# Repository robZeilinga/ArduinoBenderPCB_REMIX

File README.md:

# ArduinoBenderPCB_REMIX
Remix of PCB for Arduino controlled Wire Bender - Eagle Files

# NB NB : The PDF diagram is Mirrored! If you want to use this to make the PCB using Toner Transfer, You will need to mirror the PDF before Printing. 

A friend of mine wanted to build the AWESOME arduino controlled Wire Bender project by **How To Mechatronics**

project URL : https://howtomechatronics.com/projects/arduino-3d-wire-bending-machine/

But the provided PCB is Dual-sided. 

the PCB here is a Single Sided Version with thick tracks to help with Toner Transfer etc.

Please Note that Pin Assigments are changed if you use this PCB you will have to modify the code provided by the original project.

**Notable Changes :**

1. 7805 regulator has been removed as the Arduino NANO can regulate 12V with the built in regulator.
1. spare Digital pins D8 -- D12 have pads for optional pull up Resistors.
1. All Analogue Pins are broken out.
1. Stepper Driver Resolution is set via solder jumpers on the Copper side of the board.

if you use this PCB, please note the following changes need to be made in the Definition part of the Arduino Code.

ORIGINAL CODE 
-----------------
    // Define the stepper motors and the pins the will use
    AccelStepper feederStepper(1, 5, 6); // (Type:driver, STEP, DIR)
    AccelStepper zAxisStepper(1, 7, 8);
    AccelStepper benderStepper(1, 9, 10);

CHANGE TO
---------

    // Define the stepper motors and the pins the will use
    AccelStepper feederStepper(1, 6, 7); // (Type:driver, STEP, DIR)
    AccelStepper zAxisStepper(1, 4, 5);
    AccelStepper benderStepper(1, 2, 3);

LIMITATION OF LIABILITY 
-----------------------

Short version: We will not be liable for damages or losses arising from your use or inability to use the service or otherwise arising under this agreement. Please read this section carefully; it limits our obligations to you.

You understand and agree that we will not be liable to you or any third party for any loss of profits, use, goodwill, or data, or for any incidental, indirect, special, consequential or exemplary damages, however arising, that result from

the use, disclosure, or display of your User-Generated Content;
your use or inability to use the Service;
any modification, price change, suspension or discontinuance of the Service;
the Service generally or the software or systems that make the Service available;
unauthorized access to or alterations of your transmissions or data;
statements or conduct of any third party on the Service;
any other user interactions that you input or receive through your use of the Service; or
any other matter relating to the Service.
Our liability is limited whether or not we have been informed of the possibility of such damages, and even if a remedy set forth in this Agreement is found to have failed of its essential purpose. We will have no liability for any failure or delay due to matters beyond our reasonable control.

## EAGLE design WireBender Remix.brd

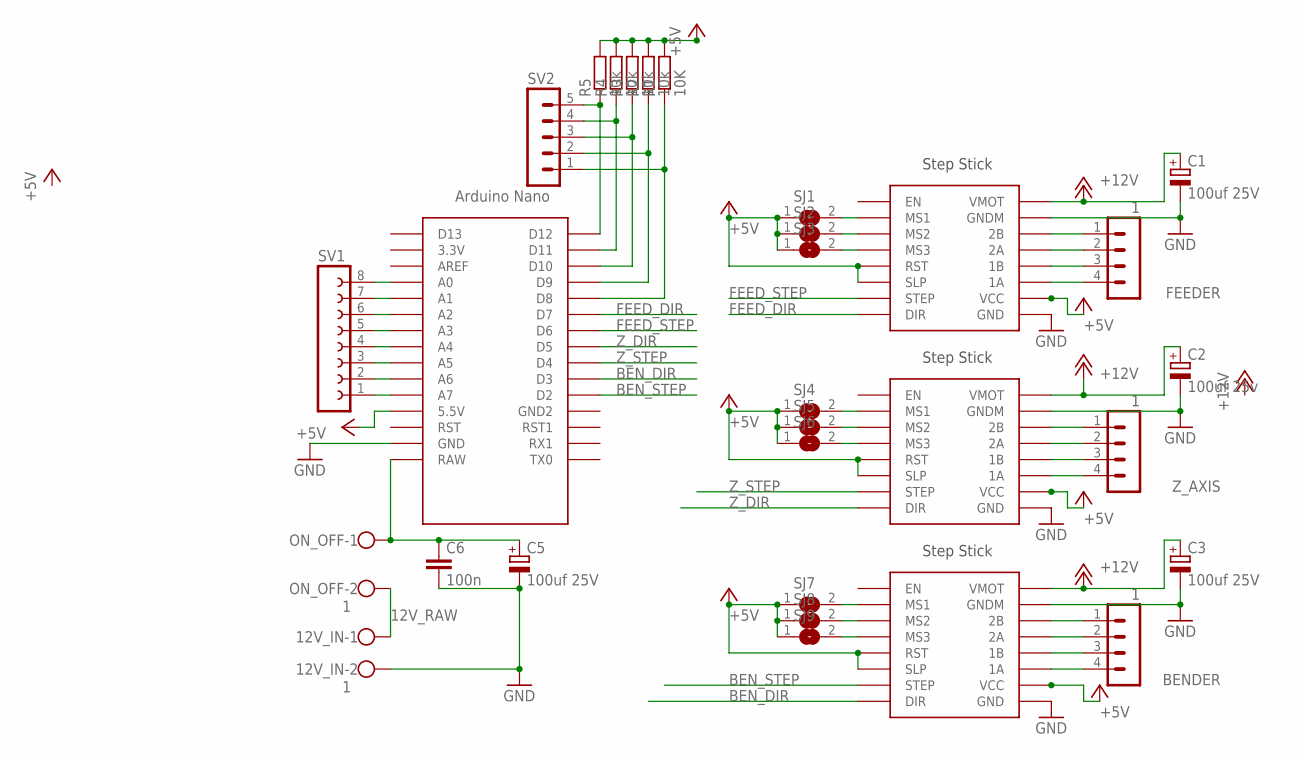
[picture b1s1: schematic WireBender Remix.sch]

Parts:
12V_IN: 1; W237-102
BENDER: 1; MA04-1
C1, C3, C5: 100uf 25V; E3,5-8
C2: 100uf 25v; E3,5-8
C6: 100n; C025-030X050
FEEDER: 1; MA04-1
FEED_DRV: STEP-STICK
ON_OFF: 1; W237-102
R1: 10K; 0207/7
R2, R3, R4, R5: 10k; 0207/7
SJ1, SJ2, SJ3, SJ4, SJ5, SJ6, SJ7, SJ8, SJ9: SJW
SV1: FE08-1; FE08
SV2: MA05-1
U$1: NANO
U$3, U$4: STEP-STICK
Z_AXIS: 1; MA04-1

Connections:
12V_RAW: 12V_IN.1, ON_OFF.2
+5V: FEED_DRV.RST, FEED_DRV.SLP, FEED_DRV.VCC, R1.2, R2.2, R3.2, R4.2, R5.2, SJ1.1, SJ2.1, SJ3.1, SJ4.1, SJ5.1, SJ6.1, SJ7.1, SJ8.1, SJ9.1, U$1.5V (5.5V), U$3.RST, U$3.SLP, U$3.VCC, U$4.RST, U$4.SLP, U$4.VCC
+12V: C1.+, C2.+, C3.+, FEED_DRV.VMOT, U$3.VMOT, U$4.VMOT
BEN_DIR: U$1.D3, U$4.DIR
BEN_STEP: U$1.D2, U$4.SPT (STEP)
FEED_DIR: FEED_DRV.DIR, U$1.D7
FEED_STEP: FEED_DRV.SPT (STEP), U$1.D6
GND: 12V_IN.2, C1.-, C2.-, C3.-, C5.-, C6.2, FEED_DRV.GND, FEED_DRV.GNDM, U$1.GND, U$3.GND, U$3.GNDM, U$4.GND, U$4.GNDM
unnamed: BENDER.4, U$4.1A
unnamed: BENDER.3, U$4.1B
unnamed: C5.+, C6.1, ON_OFF.1, U$1.RAW
unnamed: BENDER.2, U$4.2A
unnamed: BENDER.1, U$4.2B
unnamed: U$3.1A, Z_AXIS.4
unnamed: U$3.1B, Z_AXIS.3
unnamed: U$3.2A, Z_AXIS.2
unnamed: U$3.2B, Z_AXIS.1
unnamed: FEEDER.4, FEED_DRV.1A
unnamed: FEEDER.3, FEED_DRV.1B
unnamed: FEEDER.2, FEED_DRV.2A
unnamed: FEEDER.1, FEED_DRV.2B
unnamed: FEED_DRV.MS1, SJ1.2
unnamed: FEED_DRV.MS2, SJ2.2
unnamed: FEED_DRV.MS3, SJ3.2
unnamed: SJ4.2, U$3.MS1
unnamed: SJ5.2, U$3.MS2
unnamed: SJ6.2, U$3.MS3
unnamed: SJ7.2, U$4.MS1
unnamed: SJ8.2, U$4.MS2
unnamed: SJ9.2, U$4.MS3
unnamed: SV1.1, U$1.A7
unnamed: SV1.7, U$1.A1
unnamed: SV1.6, U$1.A2
unnamed: SV1.5, U$1.A3
unnamed: SV1.4, U$1.A4
unnamed: SV1.3, U$1.A5
unnamed: SV1.2, U$1.A6
unnamed: R5.1, SV2.5, U$1.D12
unnamed: SV1.8, U$1.A0
unnamed: R4.1, SV2.4, U$1.D11
unnamed: R3.1, SV2.3, U$1.D10
unnamed: R2.1, SV2.2, U$1.D9
unnamed: R1.1, SV2.1, U$1.D8
Z_DIR: U$1.D5, U$3.DIR
Z_STEP: U$1.D4, U$3.SPT (STEP)

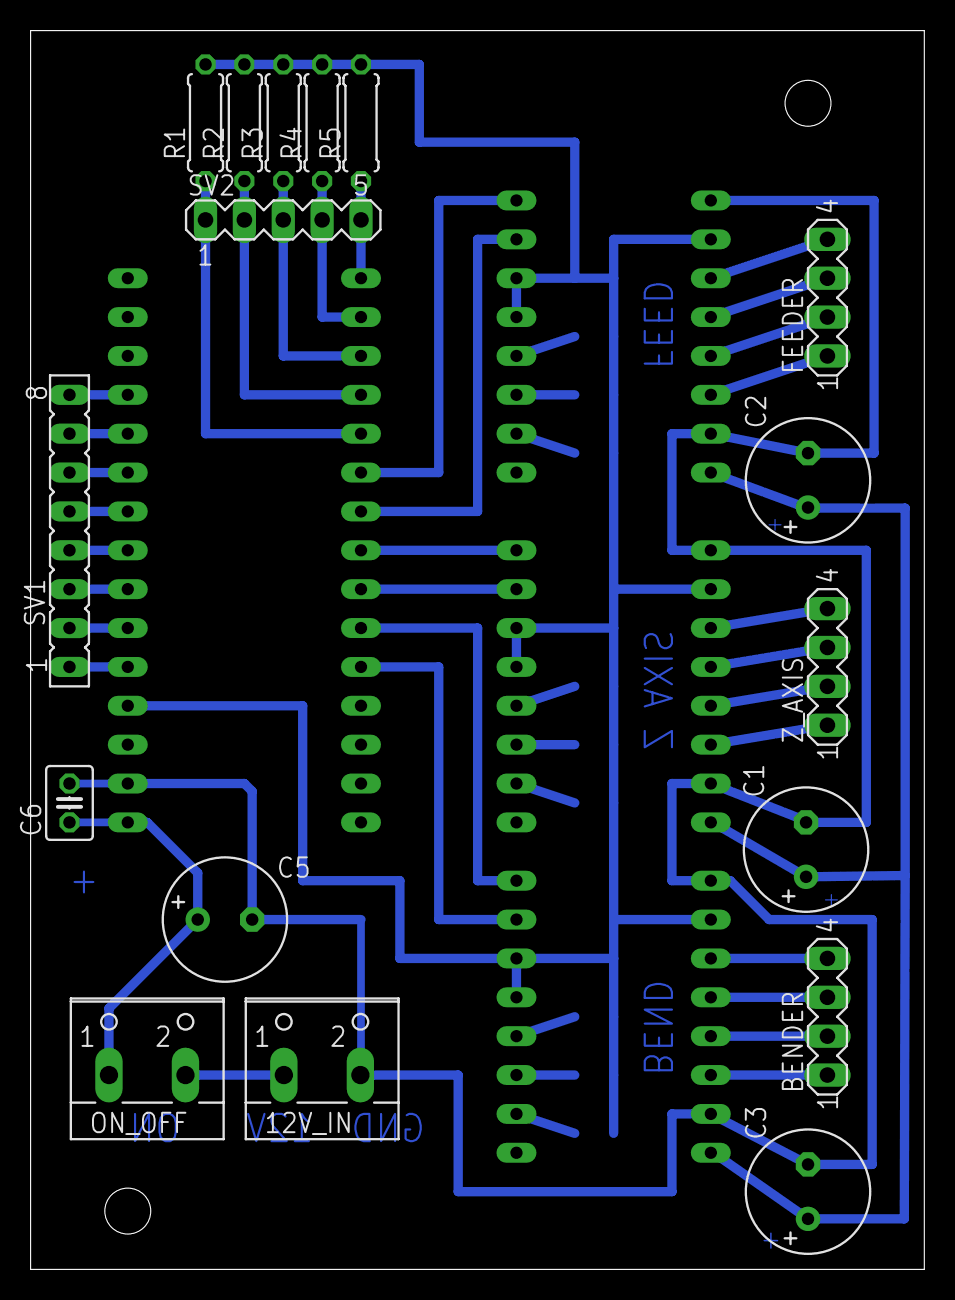
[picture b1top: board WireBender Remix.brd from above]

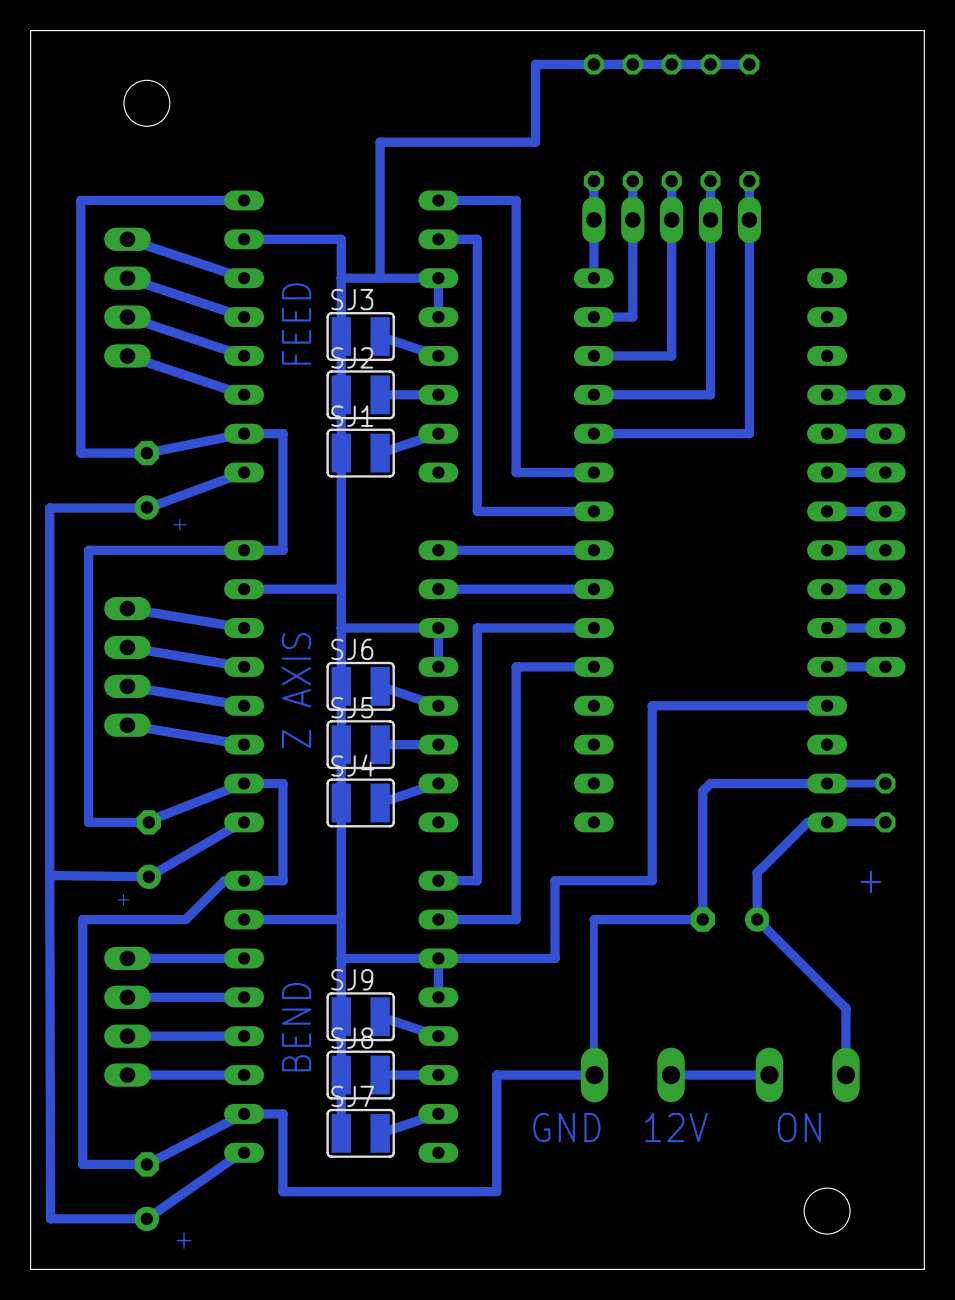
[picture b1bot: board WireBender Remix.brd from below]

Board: 2 copper layers, 58.4 x 81.0 mm, 30 parts (9 on the bottom side), 45 nets.

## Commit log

2020-02-05 added Eagle Files
2023-03-17 Update README.md
    Added Warning re Mirrored PDF
